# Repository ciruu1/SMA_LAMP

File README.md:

# SMA_LAMP

This repository contains the source code, hardware design, and documentation for an embedded systems project.

## Directory Structure

### 1. DOCS

- **Description:** This directory holds documentation related to the project.

  - **SysML:** This subdirectory contains System Modeling Language (SysML) diagrams and documentation describing the system architecture and design.

### 2. HW

- **Description:** The hardware-related files and designs are stored in this directory.

  - **SE_ejemplo:** This subdirectory includes hardware design files and documentation for the KiCad design related to the embedded systems project.

### 3. SW

- **Description:** The software source code for the embedded systems project is organized within this directory.

  - **SMA_LAMP.X:** This subdirectory holds the source code for the main module related to lamp control (MPLAB X project).

  - **Terminal:** This subdirectory contains the source code for the terminal module, which may be responsible for user interface and interaction.

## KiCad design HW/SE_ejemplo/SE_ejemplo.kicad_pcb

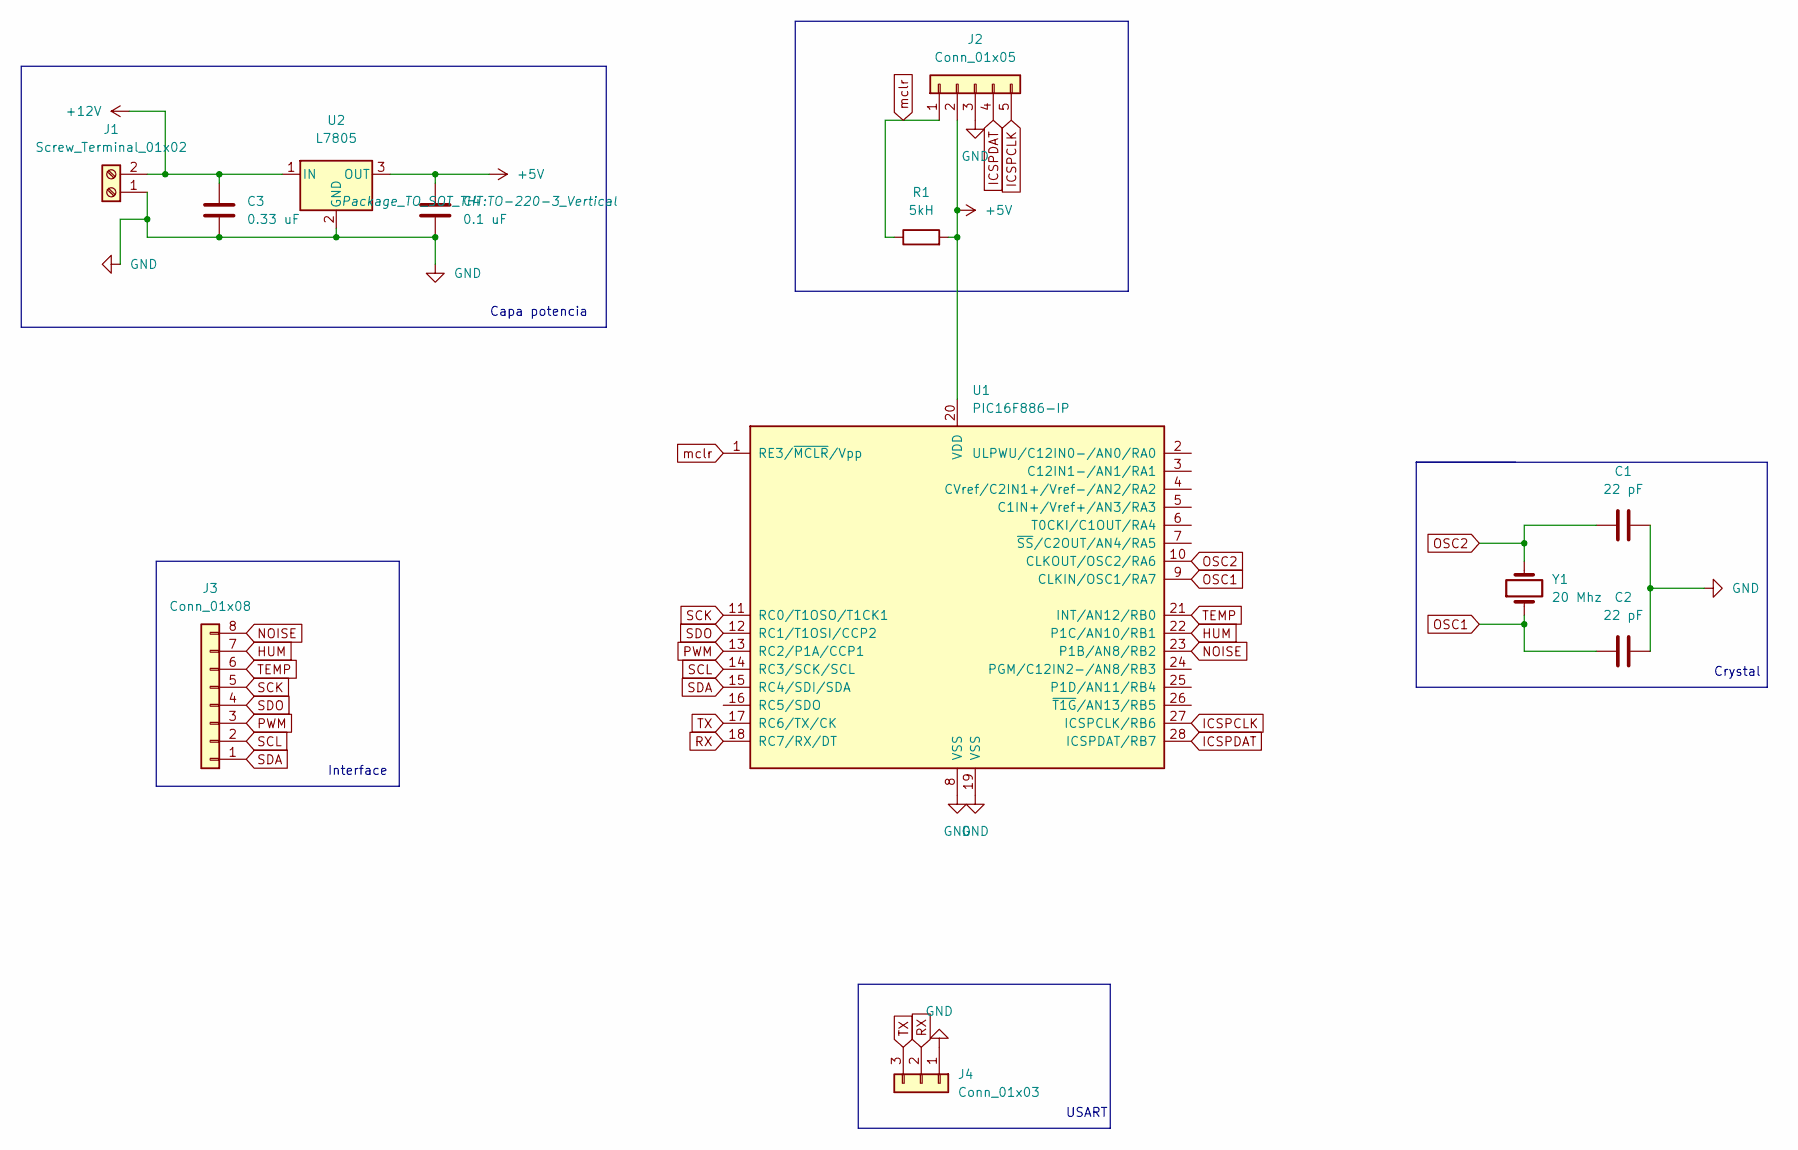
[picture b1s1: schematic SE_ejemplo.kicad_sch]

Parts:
C1, C2: 22 pF; C_Disc_D3.8mm_W2.6mm_P2.50mm
C3: 0.33 uF; CP_Radial_D5.0mm_P2.50mm
C4: 0.1 uF; CP_Radial_D5.0mm_P2.50mm
J1: Screw_Terminal_01x02; TerminalBlock_Phoenix_MKDS-1,5-2-5.08_1x02_P5.08mm_Horizont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
J2: Conn_01x05; PinSocket_1x05_P2.54mm_Vertical
J3: Conn_01x08; PinSocket_1x08_P2.54mm_Vertical
J4: Conn_01x03; PinSocket_1x03_P2.54mm_Vertical
R1: 5kH; R_Axial_DIN0204_L3.6mm_D1.6mm_P5.08mm_Horizontal
U1: PIC16F886-IP; DIP-28_W7.62mm
U2: L7805; TO-220-3_Vertical
Y1: 20 Mhz; Crystal_HC18-U_Vertical

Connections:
+5V: C4.1, J2.2, R1.2, U1.20 (VDD), U2.3 (OUT)
+12V: C3.1, J1.2, U2.1 (IN)
GND: C1.1, C2.1, C3.2, C4.2, J1.1, J2.3, J4.1, U1.8 (VSS), U1.19 (VSS), U2.2 (GND)
HUM: J3.7, U1.22 (P1C/AN10/RB1)
ICSPCLK: J2.5, U1.27 (ICSPCLK/RB6)
ICSPDAT: J2.4, U1.28 (ICSPDAT/RB7)
NOISE: J3.8, U1.23 (P1B/AN8/RB2)
OSC1: C2.2, U1.9 (CLKIN/OSC1/RA7), Y1.1
OSC2: C1.2, U1.10 (CLKOUT/OSC2/RA6), Y1.2
PWM: J3.3, U1.13 (RC2/P1A/CCP1)
RX: J4.2, U1.18 (RC7/RX/DT)
SCK: J3.5, U1.11 (RC0/T1OSO/T1CK1)
SCL: J3.2, U1.14 (RC3/SCK/SCL)
SDA: J3.1, U1.15 (RC4/SDI/SDA)
SDO: J3.4, U1.12 (RC1/T1OSI/CCP2)
TEMP: J3.6, U1.21 (INT/AN12/RB0)
TX: J4.3, U1.17 (RC6/TX/CK)
mclr: J2.1, R1.1, U1.1 (RE3/~MCLR/Vpp)

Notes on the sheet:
Capa potencia
Interface
Crystal
USART

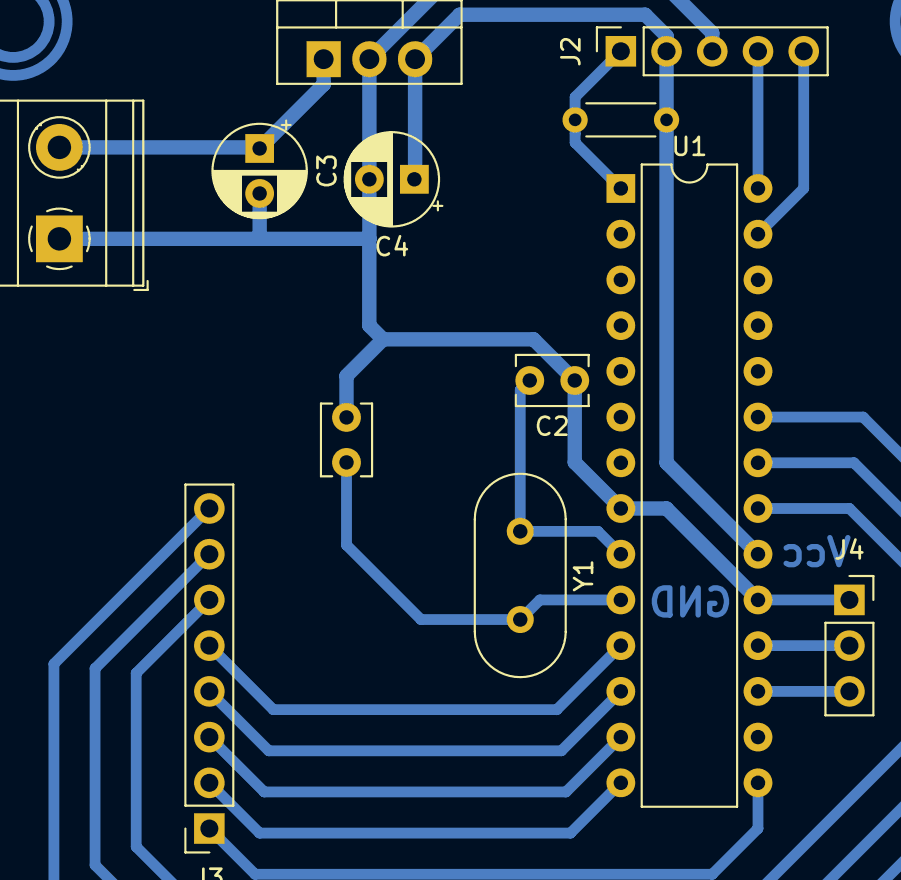
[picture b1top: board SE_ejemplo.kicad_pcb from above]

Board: 2 copper layers, 12 parts (0 on the bottom side), 18 nets.

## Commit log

2023-11-23 Added main blocks from HLD + SPI + UASRT config
2023-11-23 Refractor
2023-11-23 Added terminal scripts
2023-11-23 Added functions to send info from the MCU to the computer
2023-11-28 Removed header file for initall
2023-11-28 Deleted file
2023-11-28 Added State Diagram
2023-11-29 Finished State Diagram
2023-12-11 Tested some components
2023-12-11 GUI interface demo completed.
2023-12-12 Added UART receive
2023-12-13 Implemented I2C protocol. Added CO2 sensor functionality
2023-12-13 Added 2 I2C missing functions
2023-12-13 Added light sensor functionality
2023-12-15 Rewrote GUI
2023-12-15 Added LED SPI control
2023-12-15 Added PWM control
2023-12-17 Added comments and deleted useless files
2023-12-17 UART flag down by sw
2023-12-17 Improved GUI
2023-12-19 Added I2C
2023-12-20 Working system
2023-12-21 Deleted useless code
2023-12-21 Added EEPROM
2023-12-21 Almost working everything
2023-12-22 DONE
2023-12-23 Deleted useless files
2024-01-15 Updated docs
